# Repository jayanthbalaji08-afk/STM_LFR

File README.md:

# STM32 Line Follower Robot

## Overview

A custom STM32-based Line Follower Robot PCB designed using KiCad.

## Features

- STM32 microcontroller-based control
- Line sensor interface
- Motor driver interface
- Compact custom PCB
- Designed using KiCad

## Hardware

- STM32 Microcontroller
- IR Line Sensors
- Motor Driver
- DC Motors
- Power Supply
- Custom PCB

## PCB Design

The PCB was designed using KiCad, including:

- Schematic design
- Component placement
- PCB layout
- Routing
- Design rule checking (DRC)

## Project Files

This repository contains:

- `STM_LFR.kicad_pro` — KiCad project file
- `STM_LFR.kicad_sch` — Schematic
- `STM_LFR.kicad_pcb` — PCB layout

## Tools Used

- KiCad
- STM32
- PCB Design

## Hardware Components

| Component | Quantity | Purpose |
|---|---:|---|
| STM32 Blue Pill (STM32F103C8T6) | 1 | Main microcontroller |
| TB6612FNG Motor Driver | 1 | Controls two DC motors |
| Mini-360 Buck Converter | 1 | Steps down the input voltage |
| Push Button | 2 | User input |
| DIP Switch | 1 | Configuration and control |
| IR Sensor Header | 1 | Connection for line sensors |
| Power Input Terminal Block | 1 | Battery/power input |
| Motor Output Terminal Block | 2 | Left and right motor connections |

## Board Features

- STM32-based control
- Dual DC motor control using TB6612FNG
- Dedicated IR sensor interface
- On-board buck converter
- Two push buttons
- DIP switch for configuration
- Screw terminal for power input
- Screw terminals for motor outputs
- Custom PCB designed using KiCad

## Author

Jayanth Balaji

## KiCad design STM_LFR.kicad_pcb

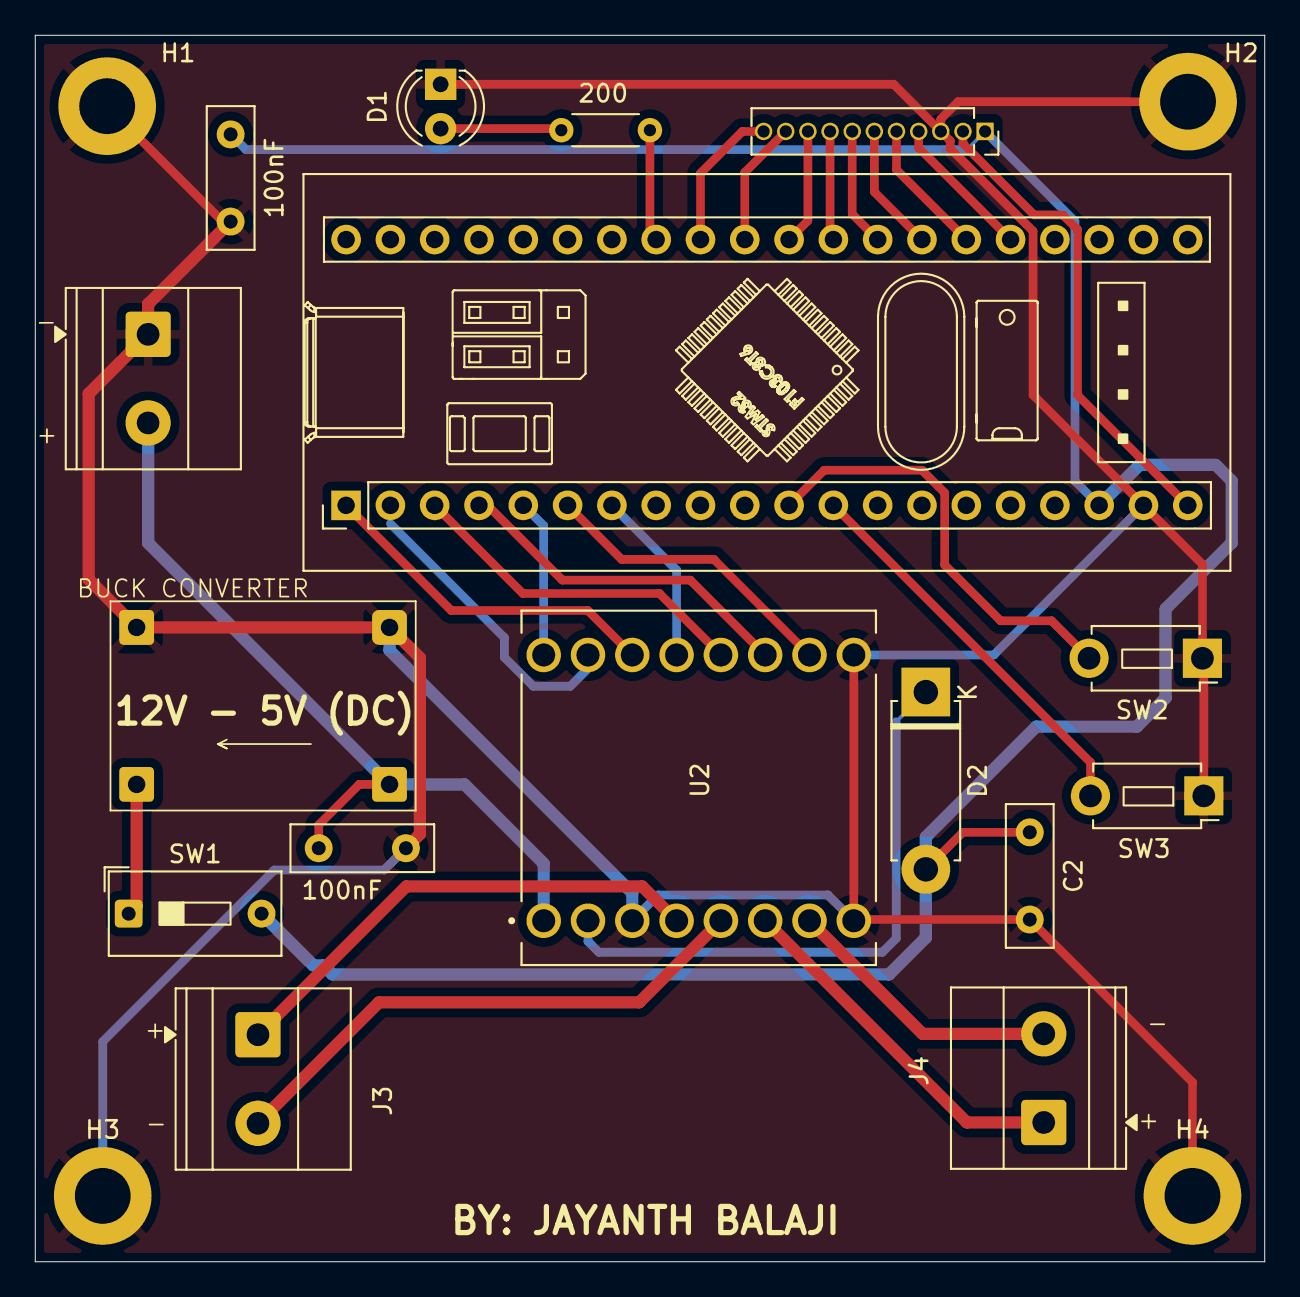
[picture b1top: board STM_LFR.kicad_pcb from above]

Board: 2 copper layers, 70.5 x 70.3 mm, 20 parts (0 on the bottom side), 29 nets.

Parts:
100nF, 100nF#2: 100nF; C_Disc_D8.0mm_W2.5mm_P5.00mm
200: R; R_Axial_DIN0204_L3.6mm_D1.6mm_P5.08mm_Horizontal
C2: 100nF; C_Disc_D8.0mm_W2.5mm_P5.00mm
D1: LED; LED_D4.0mm
D2: D; D_5W_P10.16mm_Horizontal
H1, H2, H3, H4: MountingHole_Pad; MountingHole_3.2mm_M3_DIN965_Pad
J1, J3, J4: Screw_Terminal_01x02; TerminalBlock_Phoenix_MKDS-1,5-2-5.08_1x02_P5.08mm_Horizont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
J2: Conn_01x11_Socket; PinSocket_1x11_P1.27mm_Vertical
SW1: SW_DIP_x01; SW_DIP_SPSTx01_Slide_9.78x4.72mm_W7.62mm_P2.54mm
SW2, SW3: SW_Push; SW_PUSH_1P1T_6x3.5mm_H5.0_APEM_MJTP1250
U1: BEC_5V_3A
U2: ROB-14450; MODULE_ROB-14450
U3: YAAJ_BluePill; YAAJ_BluePill_1

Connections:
1: J2.4, U3.25 (PA0)
2: J2.5, U3.26 (PA1)
3: J2.6, U3.27 (PA2)
3.3V: J2.2, U3.20 (3V3)
4: J2.7, U3.28 (PA3)
5: J2.8, U3.29 (PA4)
5V: 100nF#2.1, C2.1, D2.2 (A), J2.1, SW1.2, U3.18 (5V)
6: J2.9, U3.30 (PA5)
7: J2.10, U3.31 (PA6)
8: J2.11, U3.32 (PA7)
12V: 100nF.1, J1.2, U1.1 (VIN+), U2.1 (VM)
AIN1: U2.14 (AI1), U3.1 (PB12)
AIN2: U2.15 (AI2), U3.2 (PB13)
AO1: J3.1, U2.4 (A01)
AO2: J3.2, U2.5 (A02)
BIN1: U2.12 (BI1), U3.3 (PB14)
BIN2: U2.11 (BI2), U3.4 (PB15)
BO1: J4.2, U2.7 (B01)
BO2: J4.1, U2.6 (B02)
CALIBRATE: SW3.2, U3.12 (PB4)
GND: 100nF.2, 100nF#2.2, C2.2, D1.1 (K), H1.1, H2.1, H3.1, H4.1, J1.1, J2.3, SW2.1, SW3.1, U1.2 (VIN-), U1.4 (VOUT-), U2.3 (GND), U2.8 (GND), U2.9 (GND), U3.19 (GND)
LED: 200.2, U3.33 (PB0)
unnamed: 200.1, D1.2 (A)
unnamed: D2.1 (K), U2.2 (VCC)
unnamed: SW1.1, U1.3 (VOUT+)
PWMA: U2.16 (PWMA), U3.5 (PA8)
PWMB: U2.10 (PWMB), U3.6 (PA9)
START: SW2.2, U3.11 (PB3)
STDBY: U2.13 (STBY), U3.7 (PA10)
